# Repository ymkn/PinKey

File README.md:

# PinKey

A condensed 60% hot swappable custom mechanical keyboard powered by RP2040-Zero.

## Default Layout

You can customize the layout with [Vial](https://get.vial.today/) configurator.

Spacebar can be swap 3u to 2.25/2.75u with 2u stabilizers if you don't have 3u spacebar and its stabilizers.

## Build Guide

See [doc/buildguide.md](doc/buildguide.md)

## LICENSE

This project is licensed under the MIT License, see the [LICENSE file](LICENSE) for details.

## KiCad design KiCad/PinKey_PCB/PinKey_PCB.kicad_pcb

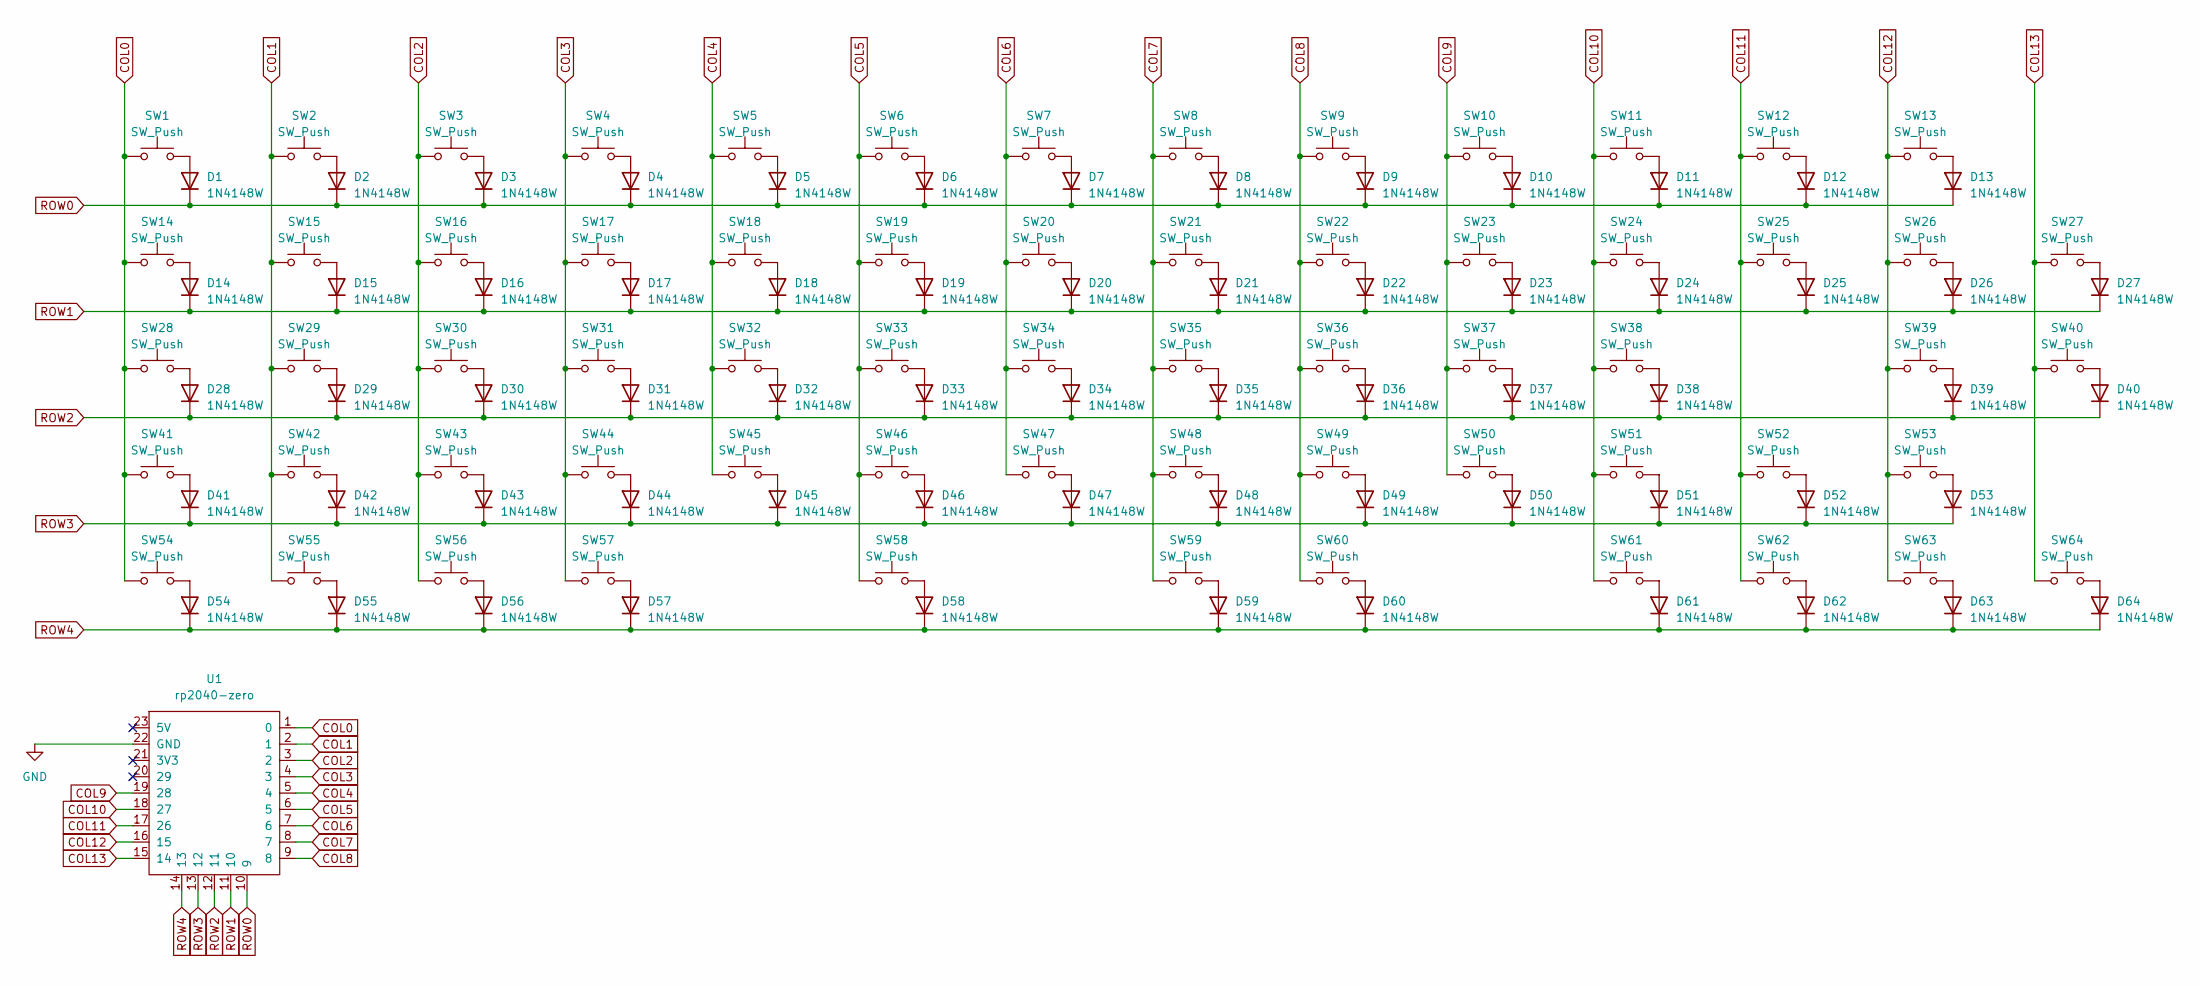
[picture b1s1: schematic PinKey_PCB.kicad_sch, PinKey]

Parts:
D1, D2, D3, D4, D5, D6, D7, D8, D9, D10, D11, D12, D13, D14, D15, D16, D17, D18, D19, D20, D21, D22, D23, D24, D25, D26, D27, D28, D29, D30, D31, D32, D33, D34, D35, D36, D37, D38, D39, D40, D41, D42, D43, D44, D45, D46, D47, D48, D49, D50, D51, D52, D53, D54, D55, D56, D57, D58, D59, D60, D61, D62, D63, D64: 1N4148W; D_SOD-123
SW1, SW2, SW3, SW4, SW5, SW6, SW7, SW8, SW9, SW10, SW11, SW12, SW13, SW15, SW16, SW17, SW18, SW19, SW20, SW21, SW22, SW23, SW24, SW26, SW27, SW29, SW30, SW31, SW32, SW33, SW34, SW35, SW36, SW37, SW39, SW40, SW42, SW43, SW44, SW45, SW46, SW47, SW48, SW49, SW50, SW51, SW52, SW53, SW62, SW63, SW64: SW_Push; SW_Hotswap_Kailh_MX_1.00u
SW14, SW25, SW54: SW_Push; SW_Hotswap_Kailh_MX_1.50u
SW28: SW_Push; SW_Hotswap_Kailh_MX_1.75u
SW38: SW_Push; SW_Hotswap_Kailh_MX_2.25u
SW41: SW_Push; SW_Hotswap_Kailh_MX_2.00u
SW55, SW56, SW57, SW59, SW60, SW61: SW_Push; SW_Hotswap_Kailh_MX_1.25u
SW58: SW_Push; SW_Hotswap_Kailh_MX_3.00u
U1: rp2040-zero; rp2040-zero-tht

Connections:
COL0: SW1.1, SW14.1, SW28.1, SW41.1, SW54.1, U1.1 (0)
COL1: SW2.1, SW15.1, SW29.1, SW42.1, SW55.1, U1.2 (1)
COL2: SW3.1, SW16.1, SW30.1, SW43.1, SW56.1, U1.3 (2)
COL3: SW4.1, SW17.1, SW31.1, SW44.1, SW57.1, U1.4 (3)
COL4: SW5.1, SW18.1, SW32.1, SW45.1, U1.5 (4)
COL5: SW6.1, SW19.1, SW33.1, SW46.1, SW58.1, U1.6 (5)
COL6: SW7.1, SW20.1, SW34.1, SW47.1, U1.7 (6)
COL7: SW8.1, SW21.1, SW35.1, SW48.1, SW59.1, U1.8 (7)
COL8: SW9.1, SW22.1, SW36.1, SW49.1, SW60.1, U1.9 (8)
COL9: SW10.1, SW23.1, SW37.1, SW50.1, U1.19 (28)
COL10: SW11.1, SW24.1, SW38.1, SW51.1, SW61.1, U1.18 (27)
COL11: SW12.1, SW25.1, SW52.1, SW62.1, U1.17 (26)
COL12: SW13.1, SW26.1, SW39.1, SW53.1, SW63.1, U1.16 (15)
COL13: SW27.1, SW40.1, SW64.1, U1.15 (14)
GND: U1.22 (GND)
unnamed: D1.2 (A), SW1.2
unnamed: D2.2 (A), SW2.2
unnamed: D3.2 (A), SW3.2
unnamed: D4.2 (A), SW4.2
unnamed: D5.2 (A), SW5.2
unnamed: D6.2 (A), SW6.2
unnamed: D7.2 (A), SW7.2
unnamed: D8.2 (A), SW8.2
unnamed: D9.2 (A), SW9.2
unnamed: D10.2 (A), SW10.2
unnamed: D11.2 (A), SW11.2
unnamed: D12.2 (A), SW12.2
unnamed: D13.2 (A), SW13.2
unnamed: D14.2 (A), SW14.2
unnamed: D15.2 (A), SW15.2
unnamed: D16.2 (A), SW16.2
unnamed: D17.2 (A), SW17.2
unnamed: D18.2 (A), SW18.2
unnamed: D19.2 (A), SW19.2
unnamed: D20.2 (A), SW20.2
unnamed: D21.2 (A), SW21.2
unnamed: D22.2 (A), SW22.2
unnamed: D23.2 (A), SW23.2
unnamed: D24.2 (A), SW24.2
unnamed: D25.2 (A), SW25.2
unnamed: D26.2 (A), SW26.2
unnamed: D27.2 (A), SW27.2
unnamed: D28.2 (A), SW28.2
unnamed: D29.2 (A), SW29.2
unnamed: D30.2 (A), SW30.2
unnamed: D31.2 (A), SW31.2
unnamed: D32.2 (A), SW32.2
unnamed: D33.2 (A), SW33.2
unnamed: D34.2 (A), SW34.2
unnamed: D35.2 (A), SW35.2
unnamed: D36.2 (A), SW36.2
unnamed: D37.2 (A), SW37.2
unnamed: D38.2 (A), SW38.2
unnamed: D39.2 (A), SW39.2
unnamed: D40.2 (A), SW40.2
unnamed: D41.2 (A), SW41.2
unnamed: D42.2 (A), SW42.2
unnamed: D43.2 (A), SW43.2
unnamed: D44.2 (A), SW44.2
unnamed: D45.2 (A), SW45.2
unnamed: D46.2 (A), SW46.2
unnamed: D47.2 (A), SW47.2
unnamed: D48.2 (A), SW48.2
unnamed: D49.2 (A), SW49.2
unnamed: D50.2 (A), SW50.2
unnamed: D51.2 (A), SW51.2
unnamed: D52.2 (A), SW52.2
unnamed: D53.2 (A), SW53.2
unnamed: D54.2 (A), SW54.2
unnamed: D55.2 (A), SW55.2
unnamed: D56.2 (A), SW56.2
unnamed: D57.2 (A), SW57.2
unnamed: D58.2 (A), SW58.2
unnamed: D59.2 (A), SW59.2
unnamed: D60.2 (A), SW60.2
unnamed: D61.2 (A), SW61.2
unnamed: D62.2 (A), SW62.2
unnamed: D63.2 (A), SW63.2
unnamed: D64.2 (A), SW64.2
ROW0: D1.1 (K), D2.1 (K), D3.1 (K), D4.1 (K), D5.1 (K), D6.1 (K), D7.1 (K), D8.1 (K), D9.1 (K), D10.1 (K), D11.1 (K), D12.1 (K), D13.1 (K), U1.10 (9)
ROW1: D14.1 (K), D15.1 (K), D16.1 (K), D17.1 (K), D18.1 (K), D19.1 (K), D20.1 (K), D21.1 (K), D22.1 (K), D23.1 (K), D24.1 (K), D25.1 (K), D26.1 (K), D27.1 (K), U1.11 (10)
ROW2: D28.1 (K), D29.1 (K), D30.1 (K), D31.1 (K), D32.1 (K), D33.1 (K), D34.1 (K), D35.1 (K), D36.1 (K), D37.1 (K), D38.1 (K), D39.1 (K), D40.1 (K), U1.12 (11)
ROW3: D41.1 (K), D42.1 (K), D43.1 (K), D44.1 (K), D45.1 (K), D46.1 (K), D47.1 (K), D48.1 (K), D49.1 (K), D50.1 (K), D51.1 (K), D52.1 (K), D53.1 (K), U1.13 (12)
ROW4: D54.1 (K), D55.1 (K), D56.1 (K), D57.1 (K), D58.1 (K), D59.1 (K), D60.1 (K), D61.1 (K), D62.1 (K), D63.1 (K), D64.1 (K), U1.14 (13)

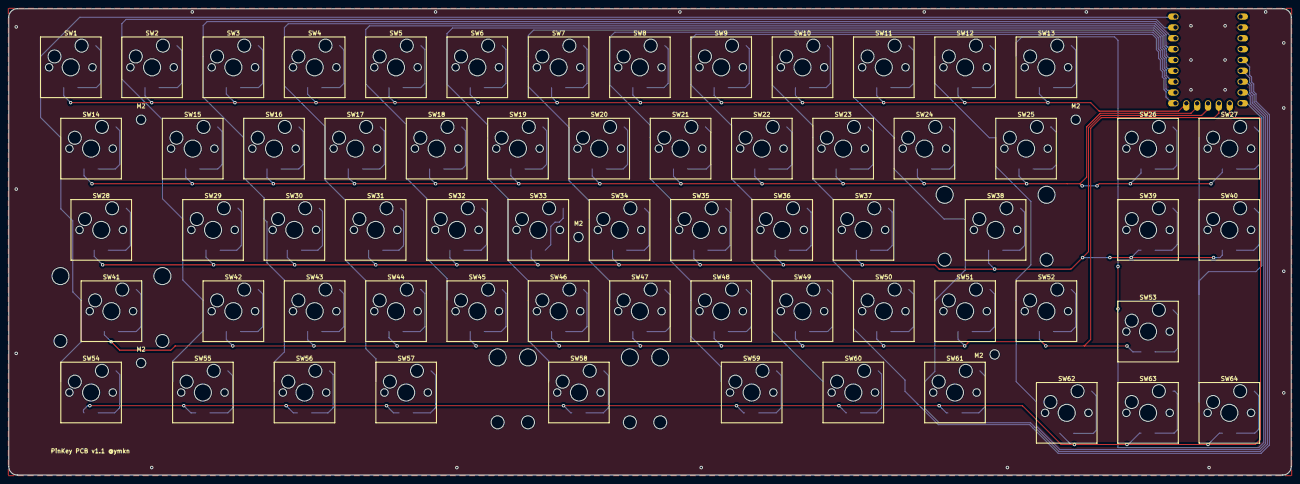
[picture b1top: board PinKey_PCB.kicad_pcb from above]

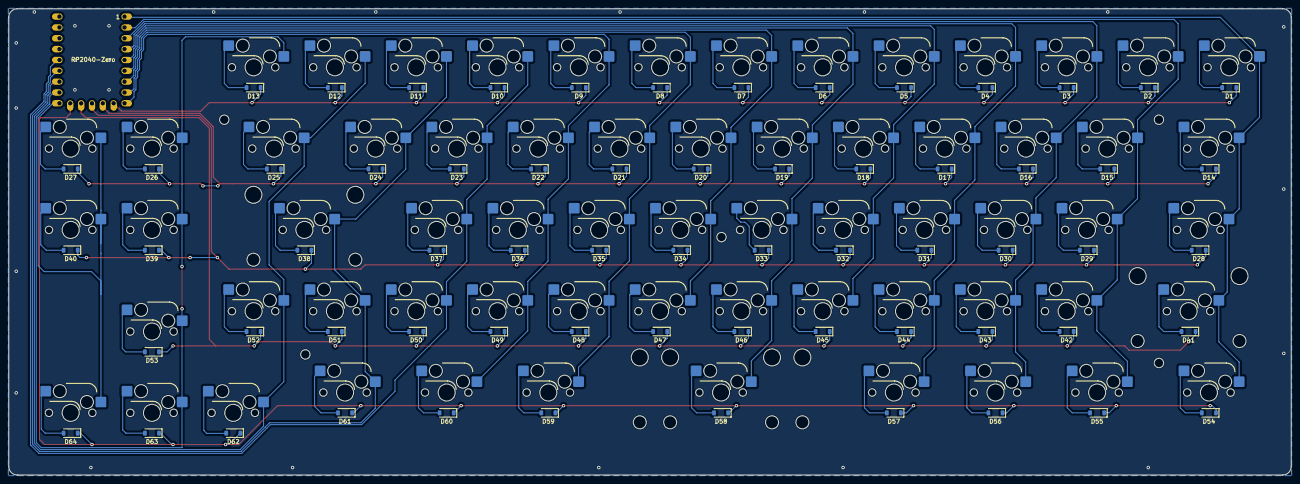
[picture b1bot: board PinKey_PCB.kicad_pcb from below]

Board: 2 copper layers, 300.5 x 109.2 mm, 134 parts (65 on the bottom side), 83 nets.

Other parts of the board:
M2, M2#2, M2#3, M2#4, M2#5: MountingHole_2.2mm_M2

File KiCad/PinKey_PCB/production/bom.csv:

Designator,Footprint,Quantity,Value,LCSC Part #
"D1, D10, D11, D12, D13, D14, D15, D16, D17, D18, D19, D2, D20, D21, D22, D23, D24, D25, D26, D27, D28, D29, D3, D30, D31, D32, D33, D34, D35, D36, D37, D38, D39, D4, D40, D41, D42, D43, D44, D45, D46, D47, D48, D49, D5, D50, D51, D52, D53, D54, D55, D56, D57, D58, D59, D6, D60, D61, D62, D63, D64, D7, D8, D9",D_SOD-123,64,1N4148W,
"SW1, SW10, SW11, SW12, SW13, SW15, SW16, SW17, SW18, SW19, SW2, SW20, SW21, SW22, SW23, SW24, SW26, SW27, SW29, SW3, SW30, SW31, SW32, SW33, SW34, SW35, SW36, SW37, SW39, SW4, SW40, SW42, SW43, SW44, SW45, SW46, SW47, SW48, SW49, SW5, SW50, SW51, SW52, SW53, SW6, SW62, SW63, SW64, SW7, SW8, SW9",SW_Hotswap_Kailh_MX_1.00u,51,SW_Push,
"SW14, SW25, SW54",SW_Hotswap_Kailh_MX_1.50u,3,SW_Push,
SW28,SW_Hotswap_Kailh_MX_1.75u,1,SW_Push,
SW38,SW_Hotswap_Kailh_MX_2.25u,1,SW_Push,
SW41,SW_Hotswap_Kailh_MX_2.00u,1,SW_Push,
"SW55, SW56, SW57, SW59, SW60, SW61",SW_Hotswap_Kailh_MX_1.25u,6,SW_Push,
SW58,SW_Hotswap_Kailh_MX_3.00u,1,SW_Push,
U1,rp2040-zero-tht,1,rp2040-zero,

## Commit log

2023-10-08 v1.1 メイン部と矢印部の隙間を0.25u相当に変更
2023-12-05 ビルドガイドの追加
2023-12-05 ロゴデータの位置変更
2023-12-06 ファームウェアの追加
2023-12-06 同梱ネジ数変更
2023-12-06 READMEとLICENSE追加
2023-12-09 ファイル名の大文字小文字の揺れを修正
2023-12-09 参照元の大文字小文字揺れを修正
2023-12-09 warning記法の誤りを修正
